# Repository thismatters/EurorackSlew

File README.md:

# Gated Slew

Causes V/Oct signals to gradually change between voltages with either a linear or logrithmic profile, can work on upward changes in voltage, downward, or both. Slew rate is set with knob. Gate controls whether slew is applied or not.

The circuit here is based on the [Yusynth gated slew](https://yusynth.net/Modular/EN/DUALSLEW/index.html) with minor tweaks to make it more Eurorack friendly. The changes I've made are thus:
* Selected resistors appropriate for +/-12V rails,
* Added polarity protection so that a backward power header doesn't fry anything (twin series schotty diodes: BAT54SL),
* Full surface mount design.

The Yusynth page is a treasure trove of information about this circuit that I am too amateur to claim as my own; please read that outstanding page before using this circuit. The page provides many details and other implementations of this circuit that you may find suitable.

The KiCAD project here uses the library/footprints [found in my companion repo](https://github.com/thismatters/EurorackKiCAD).

## Width

12hp on an Intellijel 1U rack.

## Inputs

Jacks for:
- V/Oct which will be slewed,
- Gate to control when slew occurs (default is always).

Knob for slew rate.

Switches for
- Linear or logrithmic slew,
- Slew on rising edge (up), falling edge (down), or both (middle).

## Outputs

Jack for V/Oct.

LED to indicate when gate is active.

## Vendors

There are part numbers in the [BOM](slew.csv) for many of the parts (not for basic passives though) at the following vendors:

* [Mouser](https://www.mouser.com): Needs no introduction. Get your ICs from here (or [digikey](https://www.digikey.com)).
* [Tayda Electronics](https://www.taydaelectronics.com/): Good supplier for passive components; audio jacks, and potentiometers. Their audio jacks are slightly smaller than the thonkiconn from thonk.
* [Love My Switches](https://lovemyswitches.com/): Has [really good knobs](https://lovemyswitches.com/anodized-aluminum-knob-the-lo-fi-1-4-smooth-shaft-12-5mm-od/) to go on those potentiometers!
* [OSHPark](https://oshpark.com/): Fast and (relatively) cheap PCB manufacturer. The [V0 circuit](https://oshpark.com/shared_projects/VN6XGUSn) works really well.

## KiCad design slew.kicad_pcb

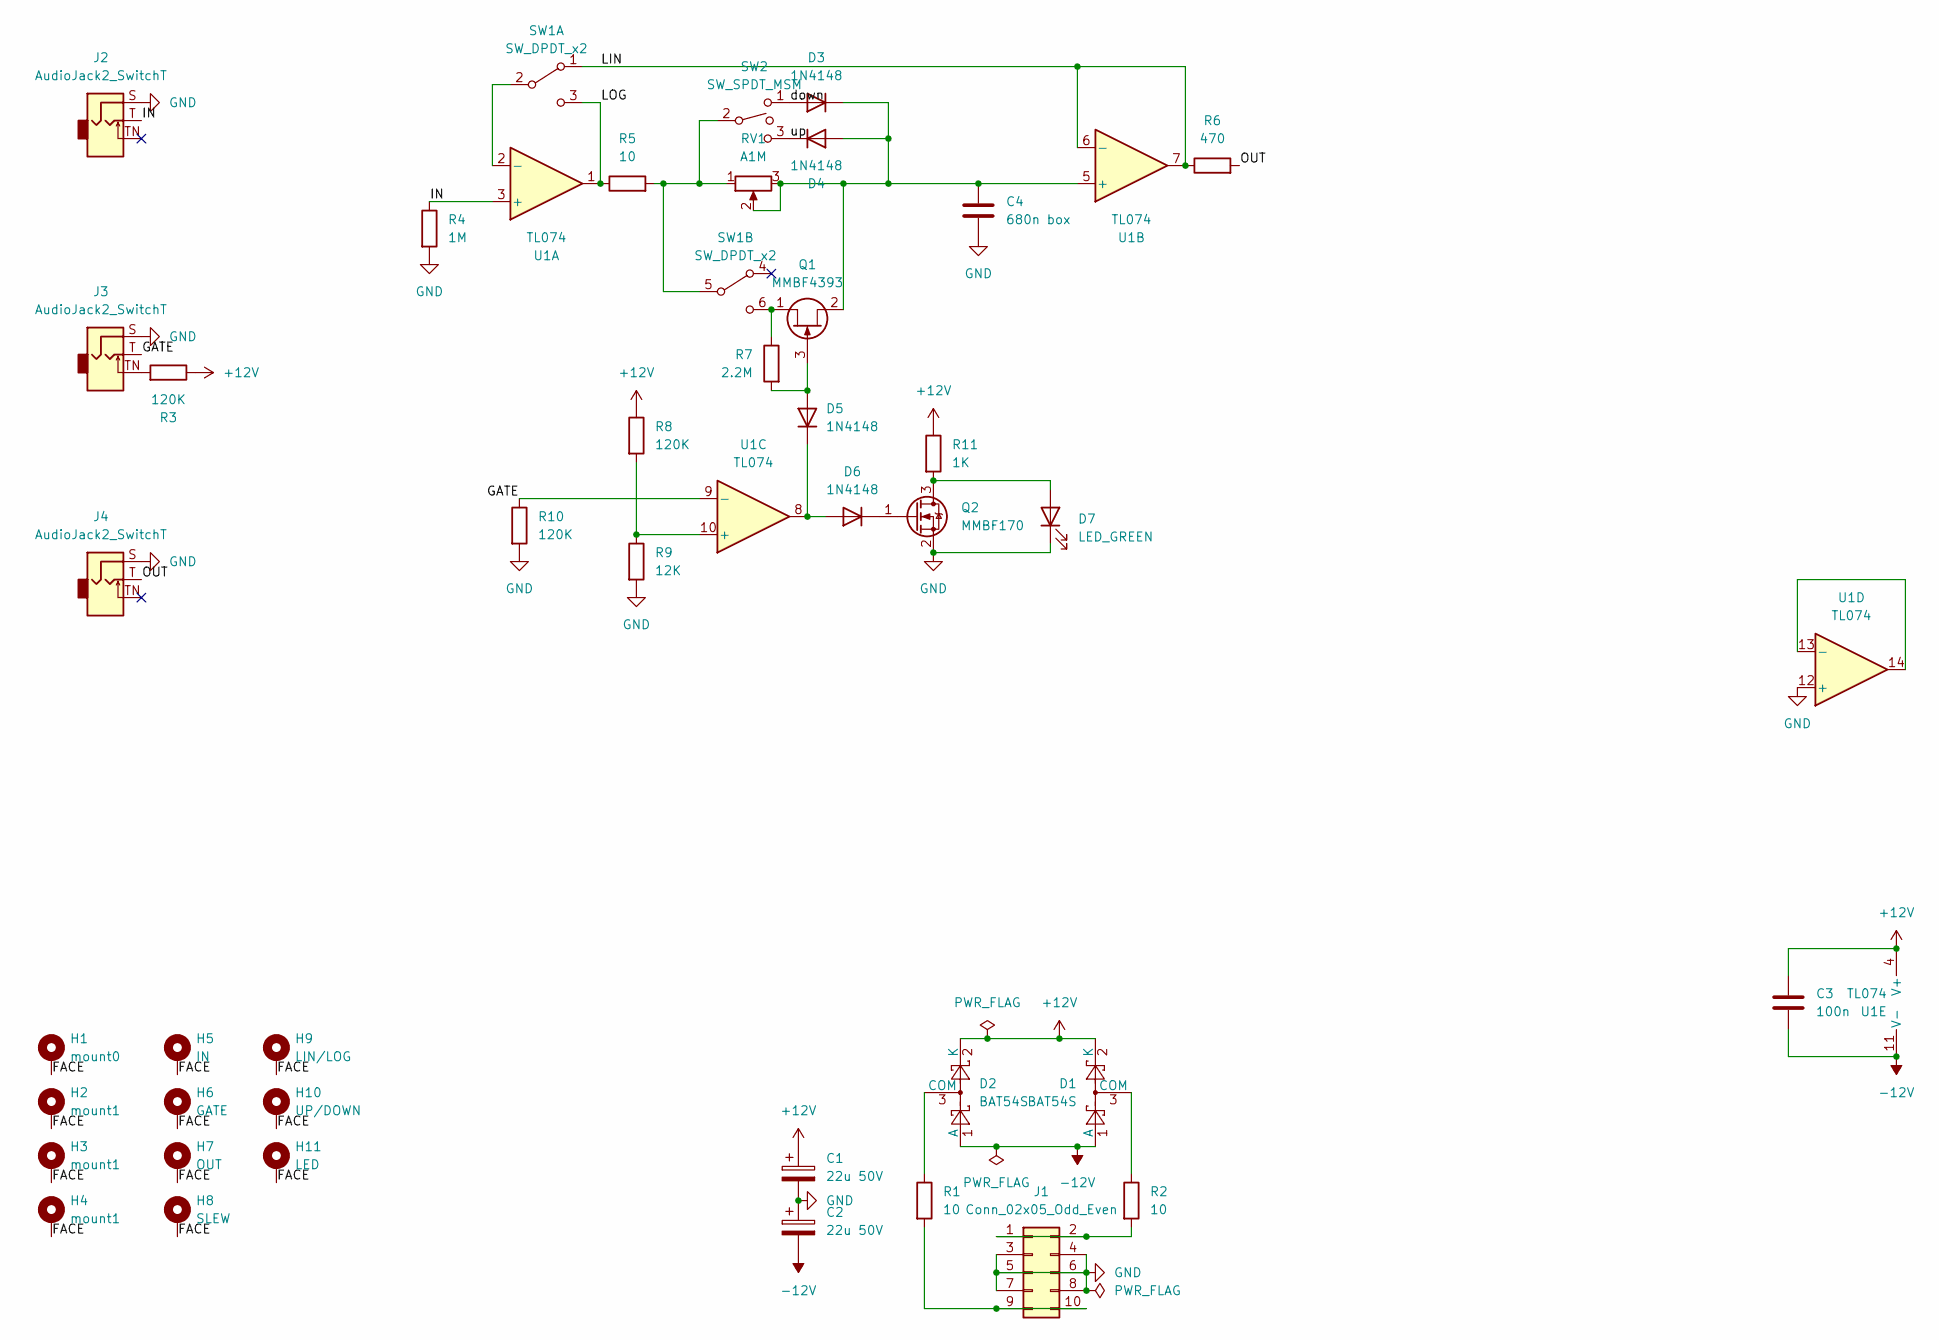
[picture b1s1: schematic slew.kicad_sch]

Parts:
C1, C2: 22u 50V; CP_Radial_D5.0mm_P2.50mm
C3: 100n; C_0805_2012Metric
C4: 680n box; C_Rect_L7.2mm_W4.5mm_P5.00mm_FKS2_FKP2_MKS2_MKP2
D1, D2: BAT54S; SOT-23; PartNum 863-BAT54SLT1G
D3, D4, D5, D6: 1N4148; D_SOD-323_HandSoldering
D7: LED_GREEN; LED_D3.0mm
H1: mount0; Mech-MountingHole
H2, H3, H4: mount1; Mech-MountingHole
H5: IN; Mech-AudioJack-Hole-Input-Voct
H6: GATE; Mech-AudioJack-Hole-Input-Gate
H7: OUT; Mech-AudioJack-Hole-Output-Voct
H8: SLEW; Mech-Potentiometer-Hole_level_90deg
H9: LIN/LOG; Mech-2M_Switch-Hole
H10: UP/DOWN; Mech-2M_Switch-Hole
H11: LED; Mech-LED-Hole-3mm-Bezel
J1: Conn_02x05_Odd_Even; PinHeader_2x05_P2.54mm_Vertical; PartNum A-2939
J2, J3, J4: AudioJack2_SwitchT; AudioJack2_Tayda_A-2566; PartNum A-2566
Q1: MMBF4393; SOT-23; PartNum 863-MMBF4393LT1G
Q2: MMBF170; SOT-23; PartNum 863-MMBF170LT1G
R1, R2, R5: 10; R_0805_2012Metric
R3, R8, R10: 120K; R_0805_2012Metric
R4: 1M; R_0805_2012Metric
R6: 470; R_0805_2012Metric
R7: 2.2M; R_0805_2012Metric
R9: 12K; R_0805_2012Metric
R11: 1K; R_0805_2012Metric
RV1: A1M; Potentiometer_RV16AF-41-15R1; PartNum A-2425
SW1: SW_DPDT_x2; Switch_DPDT_Tayda_A-5752; PartNum A-6809
SW2: SW_SPDT_MSM; Switch_SPDT_Tayda_A-5751; PartNum A-5671
U1: TL074; SOIC-14_3.9x8.7mm_P1.27mm; PartNum 595-TL074CDR

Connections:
+12V: C1.1, C3.1, D1.2 (K), D2.2 (K), R3.1, R8.1, R11.1, U1.4 (V+)
-12V: C2.2, C3.2, D1.1 (A), D2.1 (A), U1.11 (V-)
/FACE: H1.1, H2.1, H3.1, H4.1, H5.1, H6.1, H7.1, H8.1, H9.1, H10.1, H11.1
/GATE: J3.T, R10.1, U1.9 (-)
/IN: J2.T, R4.1, U1.3 (+)
/LIN: R6.1, SW1.1 (A), U1.6 (-), U1.7
/LOG: R5.1, SW1.3 (C), U1.1
/OUT: J4.T, R6.2
/down: D3.2 (A), SW2.1
/up: D4.1 (K), SW2.3
GND: C1.2, C2.1, C4.2, D7.1 (K), J1.3, J1.4, J1.5, J1.6, J1.7, J1.8, J2.S, J3.S, J4.S, Q2.2 (S), R4.2, R9.2, R10.2, U1.12 (+)
unnamed: D1.3 (COM), R2.1
unnamed: D2.3 (COM), R1.1
unnamed: C4.1, D3.1 (K), D4.2 (A), Q1.2 (S), RV1.2, RV1.3, U1.5 (+)
unnamed: D5.2 (A), Q1.3 (G), R7.2
unnamed: D5.1 (K), D6.2 (A), U1.8
unnamed: D6.1 (K), Q2.1 (G)
unnamed: D7.2 (A), Q2.3 (D), R11.2
unnamed: J1.1, J1.2, R2.2
unnamed: J1.9, J1.10, R1.2
unnamed: J3.TN, R3.2
unnamed: Q1.1 (D), R7.1, SW1.6 (C)
unnamed: SW1.2 (B), U1.2 (-)
unnamed: R5.2, RV1.1, SW1.5 (B), SW2.2
unnamed: R8.2, R9.1, U1.10 (+)
unnamed: U1.13 (-), U1.14

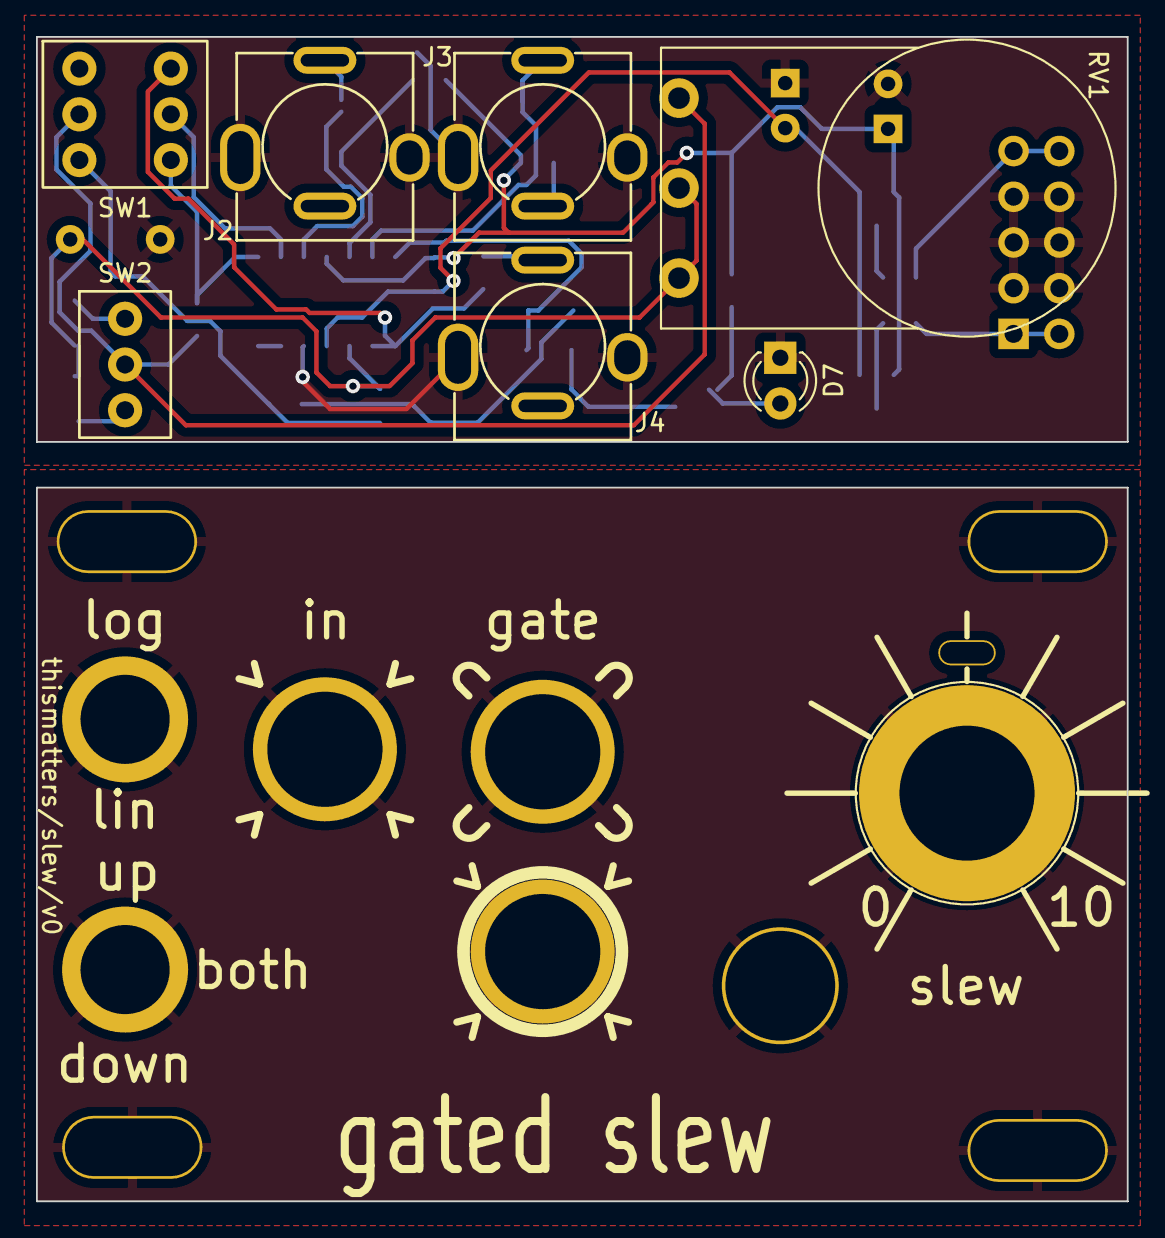
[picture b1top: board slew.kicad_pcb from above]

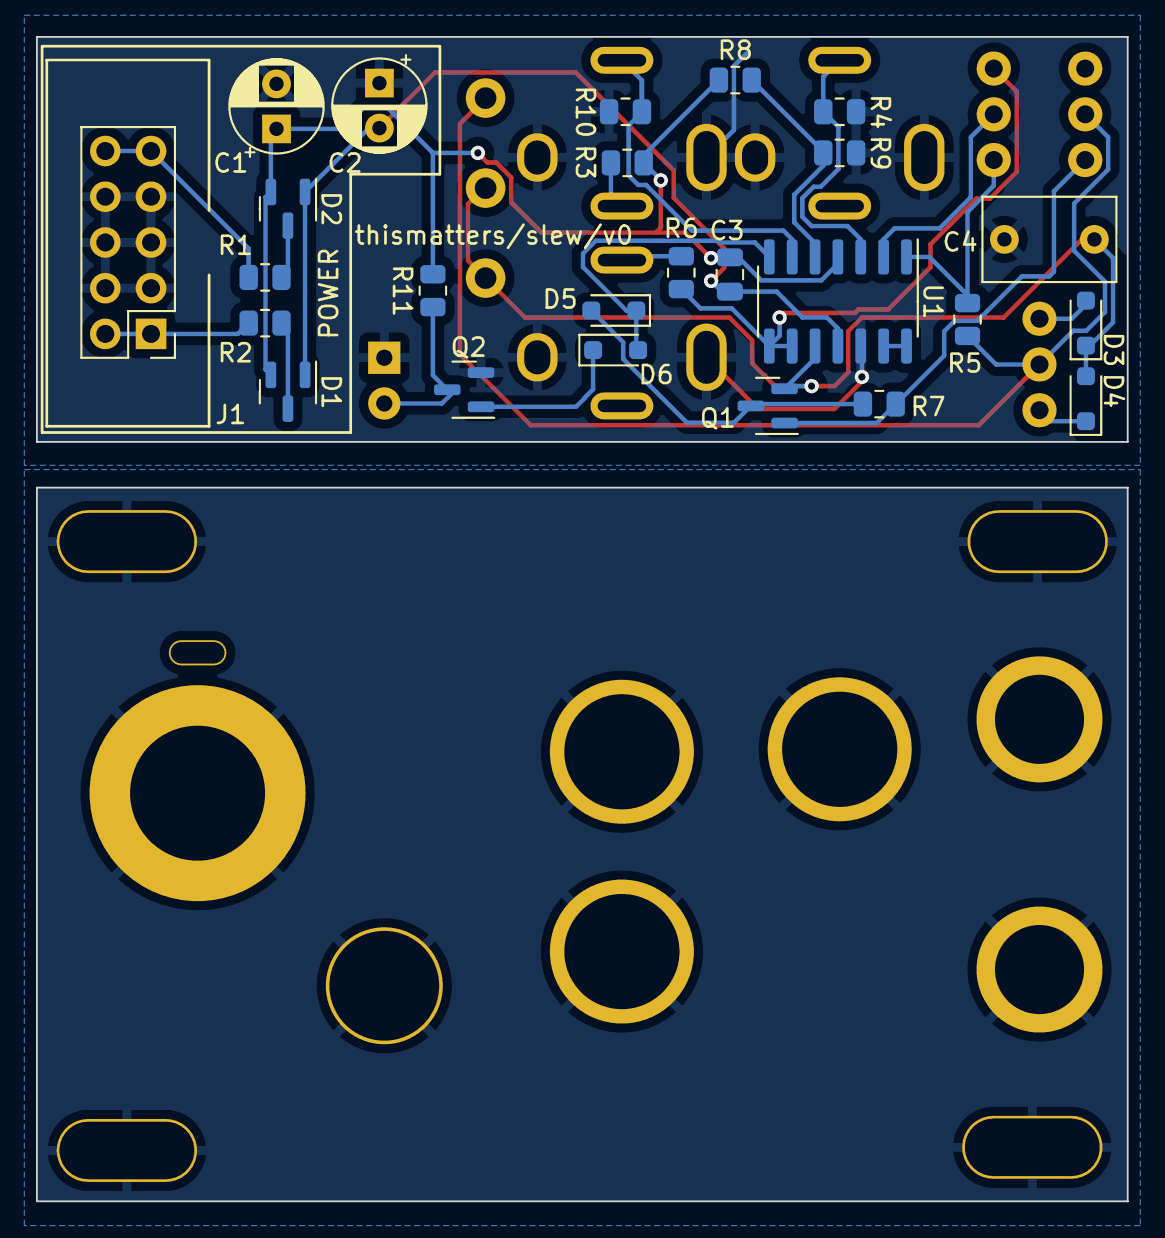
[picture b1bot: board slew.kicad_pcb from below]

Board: 2 copper layers, 60.6 x 64.7 mm, 43 parts (25 on the bottom side), 26 nets.

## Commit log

2024-11-17 adding readme
2024-11-17 fix: add link to PCB
2024-11-17 fix: add description of module
